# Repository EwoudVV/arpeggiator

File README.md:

# Arpeggiator

a standalone arpeggiator made from analog circuits and logic chips. no microcontroller or firmware

there are 12 note switches, arranged like one octave of a piano. turn on the notes in a chord and it plays them in ascending order. a 1/2/3-octave selector sets how many octaves it plays before repeating

with C, E and G selected, the two-octave setting plays C, E, G, then the same notes an octave higher, then starts again

## controls

- 12 latching note switches and note LEDs
- 1/2/3-octave range selector
- tempo knob and start/stop button
- tuning, decay, tone and volume knobs
- sawtooth/pulse waveform switch
- mono line output on a 3.5 mm jack
- regulated 12V DC, centre-positive 5.5 x 2.1 mm plug

## how it works

a clock sets the pace. a counter and logic circuit find the next selected note, skipping notes that are switched off. the note and octave are saved in a register so the pitch stays steady between steps

a precision voltage reference and resistor ladder set the note voltages. the selected voltage, plus an octave offset, controls an analog oscillator. an envelope controls each note's volume, followed by the tone control and output buffer

the controls and connectors will fit into a printed desktop case. the plan is one custom four-layer PCB, with through-hole controls and larger surface-mount parts where practical

## progress

the PCB is routed. it's 220 x 170 mm, with four layers. the controls are on the front and most of the circuit is on the back

i started with two layers, but fitting all the ground connections around the signal tracks was getting awkward. the two inner ground planes made that much easier

the printed case is drawn too, with a removable rear cover for tuning. i'm getting the parts together now

[parts list](BOM.csv) · [buy quantities and prices](PURCHASES.csv)

some of the controls don't have 3D models yet

## files

open [arpeggiator.kicad_pro](arpeggiator.kicad_pro) in KiCad. the [main schematic](arpeggiator.kicad_sch) links the circuit sheets in [schematic](schematic)

[arpeggiator.kicad_pcb](arpeggiator.kicad_pcb) is the routed board. the [case files and assembly notes](case) include the FreeCAD model, STEP assembly and printable STLs

[fabrication files](fabrication) includes the Gerbers and bottom stencil for JLCPCB. the board uses 1 oz outer copper and 0.5 oz inner copper

[design notes](DESIGN.md)

[journal](JOURNAL.md)

[Half Life project](https://halflife.hackclub.com/projects/cmvfhc9ih000001o8aysnkf0b)

*made for Hack Club Half Life, music week*

## parts

[BOM.csv](BOM.csv) lists what goes into one build. [PURCHASES.csv](PURCHASES.csv) has the pack sizes and minimum quantities from the shops. the case and knobs use my own filament

the current quotes add up to about $359. that includes estimated postage for the oscillator and acrylic rods, but not any LCSC import charges

<details>
<summary>full parts list</summary>

| qty | part | part number | supplier |
| ---: | --- | --- | --- |
| 4 | 74HC04 | 74HC04D,653 | [LCSC](https://www.lcsc.com/product-detail/C5590.html) |
| 8 | 74HC08 | 74HC08D,653 | [LCSC](https://www.lcsc.com/product-detail/C5593.html) |
| 1 | 74HC138 | 74HC138D,653 | [LCSC](https://www.lcsc.com/product-detail/C5602.html) |
| 4 | 74HC14 | 74HC14D,653 | [LCSC](https://www.lcsc.com/product-detail/C5605.html) |
| 1 | 74HC154 | CD74HC154M96 | [LCSC](https://www.lcsc.com/product-detail/C2832236.html) |
| 4 | 74HC163 | SN74HC163DR | [LCSC](https://www.lcsc.com/product-detail/C338758.html) |
| 7 | 74HC32 | 74HC32D,653 | [LCSC](https://www.lcsc.com/product-detail/C5632.html) |
| 3 | 74HC377 | 74HC377D,653 | [LCSC](https://www.lcsc.com/product-detail/C5639.html) |
| 1 | 74HC4051D | 74HC4051D,653 | [LCSC](https://www.lcsc.com/product-detail/C9386.html) |
| 4 | 74HC574 | 74HC574D,653 | [LCSC](https://www.lcsc.com/product-detail/C16501.html) |
| 3 | 74HC74 | 74HC74D,653 | [LCSC](https://www.lcsc.com/product-detail/C27597.html) |
| 2 | 74HC86 | 74HC86D,653 | [LCSC](https://www.lcsc.com/product-detail/C5955.html) |
| 1 | ADG706BRUZ | ADG706BRUZ-REEL7 | [LCSC](https://www.lcsc.com/product-detail/C408400.html) |
| 1 | AS3340A | AS3340A | [Infinite Machinery](https://infinitemachinery.com/as3340a) |
| 1 | CD74HC4067M | CD74HC4067M | [LCSC](https://www.lcsc.com/product-detail/C1545936.html) |
| 1 | L7805CV | L7805CV | [LCSC](https://www.lcsc.com/product-detail/C111887.html) |
| 1 | L7905CV | L7905CV | [LCSC](https://www.lcsc.com/product-detail/C111884.html) |
| 1 | LM13700M/NOPB | LM13700M/NOPB | [LCSC](https://www.lcsc.com/product-detail/C1346265.html) |
| 1 | LT1054CP | LT1054CP | [Mouser](https://www.mouser.com/en/ProductDetail/Texas-Instruments/LT1054CP?qs=p6YqzpSxLIw2yA3OFyb6XA%3D%3D) |
| 1 | MCP100T-450I/TT | MCP100T-450I/TT | [LCSC](https://www.lcsc.com/product-detail/C134467.html) |
| 2 | OPA4192IDR | OPA4192IDR | [LCSC](https://www.lcsc.com/product-detail/C2057908.html) |
| 1 | TL074HIDR | TL074HIDR | [LCSC](https://www.lcsc.com/product-detail/C2878713.html) |
| 2 | TL431BIDBZR | TL431BIDBZR | [LCSC](https://www.lcsc.com/product-detail/C41283.html) |
| 3 | TLC555IDR | TLC555IDR | [LCSC](https://www.lcsc.com/product-detail/C6987.html) |
| 1 | TMUX6219DGKRQ1 | TMUX6219DGKRQ1 | [LCSC](https://www.lcsc.com/product-detail/C3657022.html) |
| 1 | 1 / 2 / 3 octaves | SR2612F-0403-18R0B-D8-N | [Tayda](https://www.taydaelectronics.com/electromechanical/switches-key-pad/rotary-switch/rotary-switch-4-pole-3-position-alpha-sr2612f.html) |
| 1 | 1000u 25V | EEU-FR1E102 | [Mouser](https://www.mouser.com/en/ProductDetail/Panasonic/EEU-FR1E102?qs=Ao3mORb5HCARq2G4MnAlEQ%3D%3D) |
| 4 | 100k 0.01% 25ppm/C | RNCF0805TKT100K | [Mouser](https://www.mouser.com/en/ProductDetail/SEI-Stackpole/RNCF0805TKT100K?qs=IPgv5n7u5QbwSiCWZtnkOw%3D%3D) |
| 1 | 100k audio volume | RD901F-40-15F-A100K | [Tayda](https://www.taydaelectronics.com/100k-ohm-logarithmic-taper-potentiometer-d-shaft-pcb-9mm.html) |
| 1 | 100k coarse trim | 3296W-1-104LF | [LCSC](https://www.lcsc.com/product-detail/C48084.html) |
| 1 | 100k offset null | 3296W-1-104LF | [LCSC](https://www.lcsc.com/product-detail/C48084.html) |
| 1 | 100k tone | RD901F-40-15F-B100K | [Tayda](https://www.taydaelectronics.com/100k-ohm-linear-taper-potentiometer-d-shaft-pcb-9mm.html) |
| 1 | 100k tune | RD901F-40-15F-B100K | [Tayda](https://www.taydaelectronics.com/100k-ohm-linear-taper-potentiometer-d-shaft-pcb-9mm.html) |
| 2 | 100n film 100V 5% | R82EC3100DQ70J | [Tayda](https://www.taydaelectronics.com/0-1uf-100v-5-kemet-polyester-film-box-type-capacitor.html) |
| 2 | 100u 25V | EEU-FC1E101S | [Mouser](https://www.mouser.com/en/ProductDetail/Panasonic/EEU-FC1E101S?qs=XZT10BZ%2FaGG7SbPLggsp3w%3D%3D) |
| 4 | 10k 0.01% 25ppm/C | RNCF0805TKY10K0 | [Mouser](https://www.mouser.com/en/ProductDetail/SEI-Stackpole/RNCF0805TKY10K0?qs=FESYatJ8odKPVkqigBJMsg%3D%3D) |
| 1 | 10k tempco | 3296W-1-103LF | [Mouser](https://www.mouser.com/en/ProductDetail/Bourns/3296W-1-103LF?qs=CL3xLxiry19Id6AEaxYcng%3D%3D) |
| 1 | 1M decay | RD901F-40-15F-B1M | [Tayda](https://www.taydaelectronics.com/potentiometer-variable-resistors/rotary-potentiometer/linear/1m-ohm-linear-taper-potentiometer-d-shaft-pcb-9mm.html) |
| 1 | 1u film 63V 5% | R82DC4100DQ60J | [Tayda](https://www.taydaelectronics.com/1uf-63v-5-kemet-polyester-film-box-type-capacitor.html) |
| 1 | 2.2u film 100V 10% | MKS4D042204F00KSSD | [Tayda](https://www.taydaelectronics.com/capacitors/polyester-film-box-type-capacitors/wima-2200nf-2-2uf-100v-10-polyester-film-box-type-capacitor.html) |
| 1 | 20k HF track | 3296W-1-203LF | [LCSC](https://www.lcsc.com/product-detail/C34845.html) |
| 1 | 250k linear | RD901F-40-15F-B250K | [Tayda](https://www.taydaelectronics.com/potentiometer-variable-resistors/250k-ohm-linear-taper-potentiometer-d-shaft-pcb-9mm.html) |
| 2 | 2N7002 | 2N7002,215 | [LCSC](https://www.lcsc.com/product-detail/C65189.html) |
| 1 | 3.5mm mono line out | PJ-3001F | [Tayda](https://www.taydaelectronics.com/pj-3001f-3-5-mm-mono-phone-jack.html) |
| 1 | 470n film 63V 5% | R82DC3470AA60J | [Mouser](https://www.mouser.com/en/ProductDetail/KEMET/R82DC3470AA60J?qs=06HLYMEcjuWhk0f5YvbbSQ%3D%3D) |
| 3 | 47u 25V | 25YXJ47M5X11 | [Mouser](https://www.mouser.com/en/ProductDetail/Rubycon/25YXJ47M5X11?qs=T3oQrply3y%2F3J8S0Pc4Y1g%3D%3D) |
| 1 | 500 scale | 3296W-1-501LF | [Mouser](https://www.mouser.com/en/ProductDetail/Bourns/3296W-1-501LF?qs=jv1NtkgVBglZfwkzTzmOUg%3D%3D) |
| 1 | A | 1MS1T1B1M2QES | [Tayda](https://www.taydaelectronics.com/electromechanical/switches-key-pad/toggle-switch/mini-toggle-switch-spdt-on-none-on-pc-thru-hole.html) |
| 1 | A sharp | 1MS1T1B1M2QES | [Tayda](https://www.taydaelectronics.com/electromechanical/switches-key-pad/toggle-switch/mini-toggle-switch-spdt-on-none-on-pc-thru-hole.html) |
| 1 | AO3401A | AO3401A | [LCSC](https://www.lcsc.com/product-detail/C15127.html) |
| 1 | B | 1MS1T1B1M2QES | [Tayda](https://www.taydaelectronics.com/electromechanical/switches-key-pad/toggle-switch/mini-toggle-switch-spdt-on-none-on-pc-thru-hole.html) |
| 2 | BAT54GW | BAT54GWX | [LCSC](https://www.lcsc.com/product-detail/C5952163.html) |
| 1 | BAT54S,215 | BAT54S,215 | [LCSC](https://www.lcsc.com/product-detail/C47546.html) |
| 1 | BSS84 | BSS84,215 | [LCSC](https://www.lcsc.com/product-detail/C493579.html) |
| 1 | BZT52C8V2 | BZT52-C8V2J | [Mouser](https://www.mouser.com/en/ProductDetail/Nexperia/BZT52-C8V2J?qs=%252BEew9%252B0nqrCU1UOFPtFF2A%3D%3D) |
| 1 | C | 1MS1T1B1M2QES | [Tayda](https://www.taydaelectronics.com/electromechanical/switches-key-pad/toggle-switch/mini-toggle-switch-spdt-on-none-on-pc-thru-hole.html) |
| 1 | C sharp | 1MS1T1B1M2QES | [Tayda](https://www.taydaelectronics.com/electromechanical/switches-key-pad/toggle-switch/mini-toggle-switch-spdt-on-none-on-pc-thru-hole.html) |
| 1 | D | 1MS1T1B1M2QES | [Tayda](https://www.taydaelectronics.com/electromechanical/switches-key-pad/toggle-switch/mini-toggle-switch-spdt-on-none-on-pc-thru-hole.html) |
| 1 | D sharp | 1MS1T1B1M2QES | [Tayda](https://www.taydaelectronics.com/electromechanical/switches-key-pad/toggle-switch/mini-toggle-switch-spdt-on-none-on-pc-thru-hole.html) |
| 1 | E | 1MS1T1B1M2QES | [Tayda](https://www.taydaelectronics.com/electromechanical/switches-key-pad/toggle-switch/mini-toggle-switch-spdt-on-none-on-pc-thru-hole.html) |
| 1 | F | 1MS1T1B1M2QES | [Tayda](https://www.taydaelectronics.com/electromechanical/switches-key-pad/toggle-switch/mini-toggle-switch-spdt-on-none-on-pc-thru-hole.html) |
| 1 | F sharp | 1MS1T1B1M2QES | [Tayda](https://www.taydaelectronics.com/electromechanical/switches-key-pad/toggle-switch/mini-toggle-switch-spdt-on-none-on-pc-thru-hole.html) |
| 1 | G | 1MS1T1B1M2QES | [Tayda](https://www.taydaelectronics.com/electromechanical/switches-key-pad/toggle-switch/mini-toggle-switch-spdt-on-none-on-pc-thru-hole.html) |
| 1 | G sharp | 1MS1T1B1M2QES | [Tayda](https://www.taydaelectronics.com/electromechanical/switches-key-pad/toggle-switch/mini-toggle-switch-spdt-on-none-on-pc-thru-hole.html) |
| 1 | LM4040A25IDBZR | LM4040A25IDBZR | [LCSC](https://www.lcsc.com/product-detail/C9421.html) |
| 1 | MF-MSMF035/33X-2 / 350mA | MF-MSMF035/33X-2 | [Mouser](https://www.mouser.com/en/ProductDetail/Bourns/MF-MSMF035-33X-2?qs=CoAU%2FpHVZXxuOeHMuQc7RQ%3D%3D) |
| 2 | MMBT3904 | MMBT3904,215 | [LCSC](https://www.lcsc.com/product-detail/C426835.html) |
| 3 | MMBT3906 | MMBT3906,215 | [LCSC](https://www.lcsc.com/product-detail/C75549.html) |
| 1 | PESD5V0S1BA,115 | PESD5V0S1BA,115 | [LCSC](https://www.lcsc.com/product-detail/C19224.html) |
| 1 | PJ-102AH / 12V DC centre + | PJ-102AH | [Mouser](https://www.mouser.com/en/ProductDetail/Same-Sky/PJ-102AH?qs=WyjlAZoYn50Yq4CrVLCXLw%3D%3D) |
| 1 | SMBJ12A | SMBJ12A | [Mouser](https://www.mouser.com/en/ProductDetail/Littelfuse/SMBJ12A?qs=JJML70Qc14s9i3D6UUa43Q%3D%3D) |
| 3 | SS14 | SS14-E3/61T | [Mouser](https://www.mouser.com/en/ProductDetail/Vishay/SS14-E3-61T?qs=x2jpVgRnAtMLNL7KZbtr8g%3D%3D) |
| 1 | saw / pulse | 1MS1T1B1M2QES | [Tayda](https://www.taydaelectronics.com/electromechanical/switches-key-pad/toggle-switch/mini-toggle-switch-spdt-on-none-on-pc-thru-hole.html) |
| 1 | start / stop | B3F-4055 | [LCSC](https://www.lcsc.com/product-detail/C84931.html) |
| 1 | 1.1M 1% | RC0805FR-071M1L | [Mouser](https://www.mouser.com/en/ProductDetail/YAGEO/RC0805FR-071M1L?qs=g6xwsc4j%252B%2FrRMnxWx%2Fruqg%3D%3D) |
| 2 | 1.5M 1% | RC0805FR-071M5L | [Mouser](https://www.mouser.com/en/ProductDetail/YAGEO/RC0805FR-071M5L?qs=g6xwsc4j%252B%2FoVoMODI3Rz0Q%3D%3D) |
| 1 | 1.5k 1% | RC0805FR-071K5L | [Mouser](https://www.mouser.com/en/ProductDetail/YAGEO/RC0805FR-071K5L?qs=8Y8p%252BasKcI6LbaohOVk4HA%3D%3D) |
| 1 | 1.82M 0.1% | CPF0805B1M82E | [Mouser](https://www.mouser.com/en/ProductDetail/TE-Connectivity/CPF0805B1M82E?qs=CXI0wBT1M2hvtJld3NhfsA%3D%3D) |
| 1 | 1.8M 1% | ERJ-6ENF1804V | [Mouser](https://www.mouser.com/en/ProductDetail/Panasonic/ERJ-6ENF1804V?qs=JjxTDIFmKPTXgJmgM%2FyOiQ%3D%3D) |
| 1 | 100 0.1% | RT0805BRD07100RL | [Mouser](https://www.mouser.com/en/ProductDetail/YAGEO/RT0805BRD07100RL?qs=%2Ff7pOCXLR5dUTF5MWPONjg%3D%3D) |
| 11 | 100k 1% | RC0805FR-07100KL | [Mouser](https://www.mouser.com/en/ProductDetail/YAGEO/RC0805FR-07100KL?qs=8Y8p%252BasKcI7rEWn6FcVdAA%3D%3D) |
| 1 | 100n 5% | C0805C104J5RACTU | [Mouser](https://www.mouser.com/en/ProductDetail/KEMET/C0805C104J5RACTU?qs=gbgtKHXraGH15GhoNPXHBg%3D%3D) |
| 68 | 100n 50V X7R 10% | CC0805KRX7R9BB104 | [LCSC](https://www.lcsc.com/product-detail/C49678.html) |
| 5 | 100p C0G | C0805C101J5GACTU | [Mouser](https://www.mouser.com/en/ProductDetail/KEMET/C0805C101J5GACTU?qs=6pfgPk%252B7Yz7wCPQSSQ%2FBjg%3D%3D) |
| 2 | 10k 0.1% | RT0805BRD0710KL | [Mouser](https://www.mouser.com/en/ProductDetail/YAGEO/RT0805BRD0710KL?qs=87%2Fgv35YuOdOfU%252BBkLDVxA%3D%3D) |
| 1 | 10k 0.1% 25ppm/C | RT0805BRD0710KL | [Mouser](https://www.mouser.com/en/ProductDetail/YAGEO/RT0805BRD0710KL?qs=87%2Fgv35YuOdOfU%252BBkLDVxA%3D%3D) |
| 25 | 10k 1% | RC0805FR-0710KL | [Mouser](https://www.mouser.com/en/ProductDetail/YAGEO/RC0805FR-0710KL?qs=7bY8808IzHq6vrU3BeiiYw%3D%3D) |
| 6 | 10n | C0805C103J5GACTU | [LCSC](https://www.lcsc.com/product-detail/C2167597.html) |
| 1 | 10u 16V | GRM21BR61C106KE15L | [LCSC](https://www.lcsc.com/product-detail/C77075.html) |
| 1 | 15k 0.1% 25ppm/C | RT0805BRD0715KL | [Mouser](https://www.mouser.com/en/ProductDetail/YAGEO/RT0805BRD0715KL?qs=%2Ff7pOCXLR5foXQ1VlhQYhQ%3D%3D) |
| 1 | 174k 0.1% | RT0805BRD07174KL | [Mouser](https://www.mouser.com/en/ProductDetail/YAGEO/RT0805BRD07174KL?qs=4CyHz7GXqSj4xC7rYoRg0A%3D%3D) |
| 1 | 18.2k 1% | ERJ-6ENF1822V | [Mouser](https://www.mouser.com/en/ProductDetail/Panasonic/ERJ-6ENF1822V?qs=JjxTDIFmKPRzh6ImPVU9cQ%3D%3D) |
| 2 | 1M 1% | RC0805FR-071ML | [Mouser](https://www.mouser.com/en/ProductDetail/YAGEO/RC0805FR-071ML?qs=8Y8p%252BasKcI6wvSL4jxV1pQ%3D%3D) |
| 12 | 1k 0.1% | RT0805BRD071KL | [Mouser](https://www.mouser.com/en/ProductDetail/YAGEO/RT0805BRD071KL?qs=%2Ff7pOCXLR5e3FpClshTdPA%3D%3D) |
| 6 | 1k 1% | RC0805FR-071KL | [Mouser](https://www.mouser.com/en/ProductDetail/YAGEO/RC0805FR-071KL?qs=1ogmaHw32WJjeGY0DHXakQ%3D%3D) |
| 2 | 1n C0G | C0805C102J5GACTU | [Mouser](https://www.mouser.com/en/ProductDetail/KEMET/C0805C102J5GACTU?qs=yrVqjCObULOWvTzsHVJg1Q%3D%3D) |
| 12 | 1u 16V | CC0805KKX7R8BB105 | [Mouser](https://www.mouser.com/en/ProductDetail/YAGEO/CC0805KKX7R8BB105?qs=QENzi4TkIJ0C75LKGblEtw%3D%3D) |
| 14 | 2.2k 1% | RC0805FR-072K2L | [Mouser](https://www.mouser.com/en/ProductDetail/YAGEO/RC0805FR-072K2L?qs=CSLd874fYV2eT6iKTza3nw%3D%3D) |
| 1 | 2.32k 0.1% | RT0805BRD072K32L | [Mouser](https://www.mouser.com/en/ProductDetail/YAGEO/RT0805BRD072K32L?qs=4CyHz7GXqSgSJcxnTJ8TbQ%3D%3D) |
| 1 | 2.49k 1% | RC0805FR-072K49L | [Mouser](https://www.mouser.com/en/ProductDetail/YAGEO/RC0805FR-072K49L?qs=QrWOOBGzeCbaR%2FeulLJohg%3D%3D) |
| 1 | 200k 1% | RC0805FR-07200KL | [Mouser](https://www.mouser.com/en/ProductDetail/YAGEO/RC0805FR-07200KL?qs=8Y8p%252BasKcI4ufYuYh%252BmyZQ%3D%3D) |
| 1 | 20k 0.1% | RT0805BRD0720KL | [Mouser](https://www.mouser.com/en/ProductDetail/YAGEO/RT0805BRD0720KL?qs=87%2Fgv35YuOd%2FdRM1LyX3Lg%3D%3D) |
| 2 | 220 1% | RC0805FR-07220RL | [Mouser](https://www.mouser.com/en/ProductDetail/YAGEO/RC0805FR-07220RL?qs=KCkj9j0IqmXa4o%252BHKR6RGw%3D%3D) |
| 1 | 22k 1% | RC0805FR-0722KL | [Mouser](https://www.mouser.com/en/ProductDetail/YAGEO/RC0805FR-0722KL?qs=ngJqVwYVsdVbc7Rh0xIeHw%3D%3D) |
| 1 | 24k 1% | RC0805FR-0724KL | [Mouser](https://www.mouser.com/en/ProductDetail/YAGEO/RC0805FR-0724KL?qs=0OpHuDRjTADBsy5P0J6k2w%3D%3D) |
| 2 | 2k 0.1% | RT0805BRD072KL | [Mouser](https://www.mouser.com/en/ProductDetail/YAGEO/RT0805BRD072KL?qs=7JGxMcfkPok2189RXPA53g%3D%3D) |
| 1 | 2n C0G | C0805C202J5GACTU | [Mouser](https://www.mouser.com/en/ProductDetail/KEMET/C0805C202J5GACTU?qs=W4SVoLh3QChWIjbVvPwmQg%3D%3D) |
| 2 | 330k 0.1% | RT0805BRD07330KL | [Mouser](https://www.mouser.com/en/ProductDetail/YAGEO/RT0805BRD07330KL?qs=aZCcseWLxnuj6nToWrZKFA%3D%3D) |
| 1 | 330n 50V | C0805C334K5RACTU | [Mouser](https://www.mouser.com/en/ProductDetail/KEMET/C0805C334K5RACTU?qs=nRD1PKnFC2Hh3tSy%2FGeH2Q%3D%3D) |
| 1 | 33k 1% | RC0805FR-0733KL | [Mouser](https://www.mouser.com/en/ProductDetail/YAGEO/RC0805FR-0733KL?qs=BrN8wpjQTgGzZxKgikrwvw%3D%3D) |
| 1 | 33p C0G | C0805C330J5GACTU | [Mouser](https://www.mouser.com/en/ProductDetail/KEMET/C0805C330J5GACTU?qs=PVnqbTyV3SUE6Uu%252BkD9Iyg%3D%3D) |
| 1 | 360k 0.1% | RT0805BRD07360KL | [Mouser](https://www.mouser.com/en/ProductDetail/YAGEO/RT0805BRD07360KL?qs=aZCcseWLxnvpELpsSQnh8g%3D%3D) |
| 1 | 36k 1% | RC0805FR-0736KL | [Mouser](https://www.mouser.com/en/ProductDetail/YAGEO/RC0805FR-0736KL?qs=g6xwsc4j%252B%2Fq3CmSeyDlL7g%3D%3D) |
| 1 | 4.7 1% 0.25W | RC1206FR-074R7L | [Mouser](https://www.mouser.com/en/ProductDetail/YAGEO/RC1206FR-074R7L?qs=bz%2FLPVPAsTK5WyYax3BLuA%3D%3D) |
| 1 | 4.7u 25V X7R | GRM21BR71E475KA73L | [LCSC](https://www.lcsc.com/product-detail/C162427.html) |
| 2 | 470 1% | RC0805FR-07470RL | [Mouser](https://www.mouser.com/en/ProductDetail/YAGEO/RC0805FR-07470RL?qs=CSLd874fYV2wsnqMGLpcHA%3D%3D) |
| 5 | 47k 1% | RC0805FR-0747KL | [Mouser](https://www.mouser.com/en/ProductDetail/YAGEO/RC0805FR-0747KL?qs=sfaR5EV1ye7DERH7OnC2Gg%3D%3D) |
| 1 | 5.62k 0.1% | RT0805BRD075K62L | [Mouser](https://www.mouser.com/en/ProductDetail/YAGEO/RT0805BRD075K62L?qs=ylEn6CkgxuiWDc5aTJ638g%3D%3D) |
| 1 | 51k 1% | RC0805FR-0751KL | [Mouser](https://www.mouser.com/en/ProductDetail/YAGEO/RC0805FR-0751KL?qs=g6xwsc4j%252B%2FrUFmy6S6ALYQ%3D%3D) |
| 1 | 6.04k 0.1% | RT0805BRD076K04L | [Mouser](https://www.mouser.com/en/ProductDetail/YAGEO/RT0805BRD076K04L?qs=8SI67b7NHM5NwjLBwcP%252BXQ%3D%3D) |
| 1 | 6.49k 0.1% | RT0805BRD076K49L | [Mouser](https://www.mouser.com/en/ProductDetail/YAGEO/RT0805BRD076K49L?qs=4CyHz7GXqSiLdN4y1MhhhQ%3D%3D) |
| 1 | 820k 1% | RC0805FR-07820KL | [Mouser](https://www.mouser.com/en/ProductDetail/YAGEO/RC0805FR-07820KL?qs=g6xwsc4j%252B%2FozLzDoZP6Szg%3D%3D) |
| 2 | 910 1% | RC0805FR-07910RL | [Mouser](https://www.mouser.com/en/ProductDetail/YAGEO/RC0805FR-07910RL?qs=g6xwsc4j%252B%2FoZ2NamZOKACA%3D%3D) |
| 6 | copper test pad | - | with PCB |
| 1 | logic test header | M20-9990846 | [Mouser](https://www.mouser.com/en/ProductDetail/Harwin/M20-9990846?qs=ulE8k0yEMYb37YKanNqd%2FQ%3D%3D) |
| 12 | note LED, 0805 | APT2012SYCK | [Mouser](https://www.mouser.com/en/ProductDetail/Kingbright/APT2012SYCK?qs=y3UkhjaxUTb%252BLZXQu8d2yw%3D%3D) |
| 1 | four-layer PCB, 220 x 170 mm, 1.6 mm FR4, 1 oz outer / 0.5 oz inner | arpeggiator-jlcpcb | [JLCPCB](https://jlcpcb.com/pcb-fabrication/fr4-pcb) |
| 1 | printed tray, control panel, rear cover and octave collar | - | printed |
| 5 | printed pot knob | - | printed |
| 1 | regulated 12V DC adapter, >=0.5A, centre +, 5.5/2.1mm | SMI6B-12-4-P5 | [Mouser](https://www.mouser.com/en/ProductDetail/CUI-Inc/SMI6B-12-4-P5?qs=mAH9sUMRCtt8%252BS4f4Sapgw%3D%3D) |
| 1 | printed octave knob | - | printed |
| 18 | M3 x 8 mm socket-head screw | A-6393 | [Tayda](https://www.taydaelectronics.com/hardware-tools/nuts-washers-screws-spacers-and-more/screws/m3-hexagon-socket-head-cap-screw-3x8mm-grade-12-9.html) |
| 18 | M3 hex nut | Nut M3 | [Tayda](https://www.taydaelectronics.com/nut-3mm-for-screw-m3.html) |
| 4 | stick-on rubber foot, about 12 mm diameter | RF-1204 | [Tayda](https://www.taydaelectronics.com/rubber-feet-black-64pcs-block-size-12mmx4mm-for-enclosure.html) |
| 1 | clear 3 mm acrylic rod, at least 200 mm stock | a24061900ux1460 | [Harfington](https://www.harfington.com/products/p-1536182) |
| 1 | round black button cap | B32-1610 | [Mouser](https://www.mouser.com/en/ProductDetail/Aratas/B32-1610?qs=1tDaWCEHQQ6l3s6oDrKSiA%3D%3D) |
| 5 | M7 x 0.75 thin pot nut and washer | - | control hardware |
| 13 | 1/4-40 toggle nut and washer | - | control hardware |
| 1 | 3/8-32 NEF rotary nut and lockwasher | - | control hardware |
| 1 | M6 x 0.5 jack nut and washer | - | control hardware |
| 1 | bottom-side frameless stencil, 380 x 280 mm, 0.12 mm | arpeggiator-bottom-stencil | [JLCPCB](https://jlcpcb.com/pcb-stencil) |

</details>

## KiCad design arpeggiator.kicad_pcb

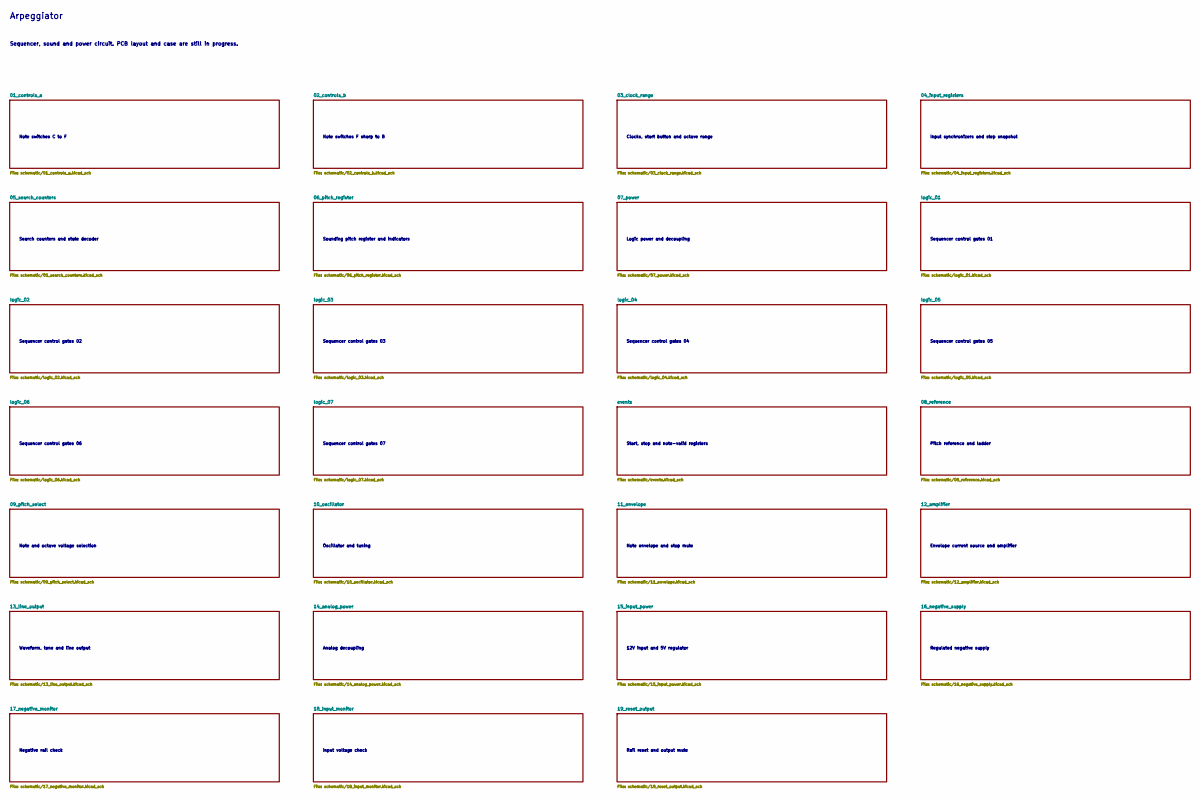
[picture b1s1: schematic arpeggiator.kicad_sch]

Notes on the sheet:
Arpeggiator
Sequencer, sound and power circuit. PCB layout and case are still in progress.
Note switches C to F
Note switches F sharp to B
Clocks, start button and octave range
Input synchronizers and step snapshot
Search counters and state decoder
Sounding pitch register and indicators
Logic power and decoupling
Sequencer control gates 01
Sequencer control gates 02
Sequencer control gates 03
Sequencer control gates 04
Sequencer control gates 05
Sequencer control gates 06
Sequencer control gates 07
Start, stop and note-valid registers
Pitch reference and ladder
Note and octave voltage selection
Oscillator and tuning
Note envelope and stop mute
Envelope current source and amplifier
Waveform, tone and line output
Analog decoupling
12V input and 5V regulator
Regulated negative supply
Negative rail check
Input voltage check
Rail reset and output mute

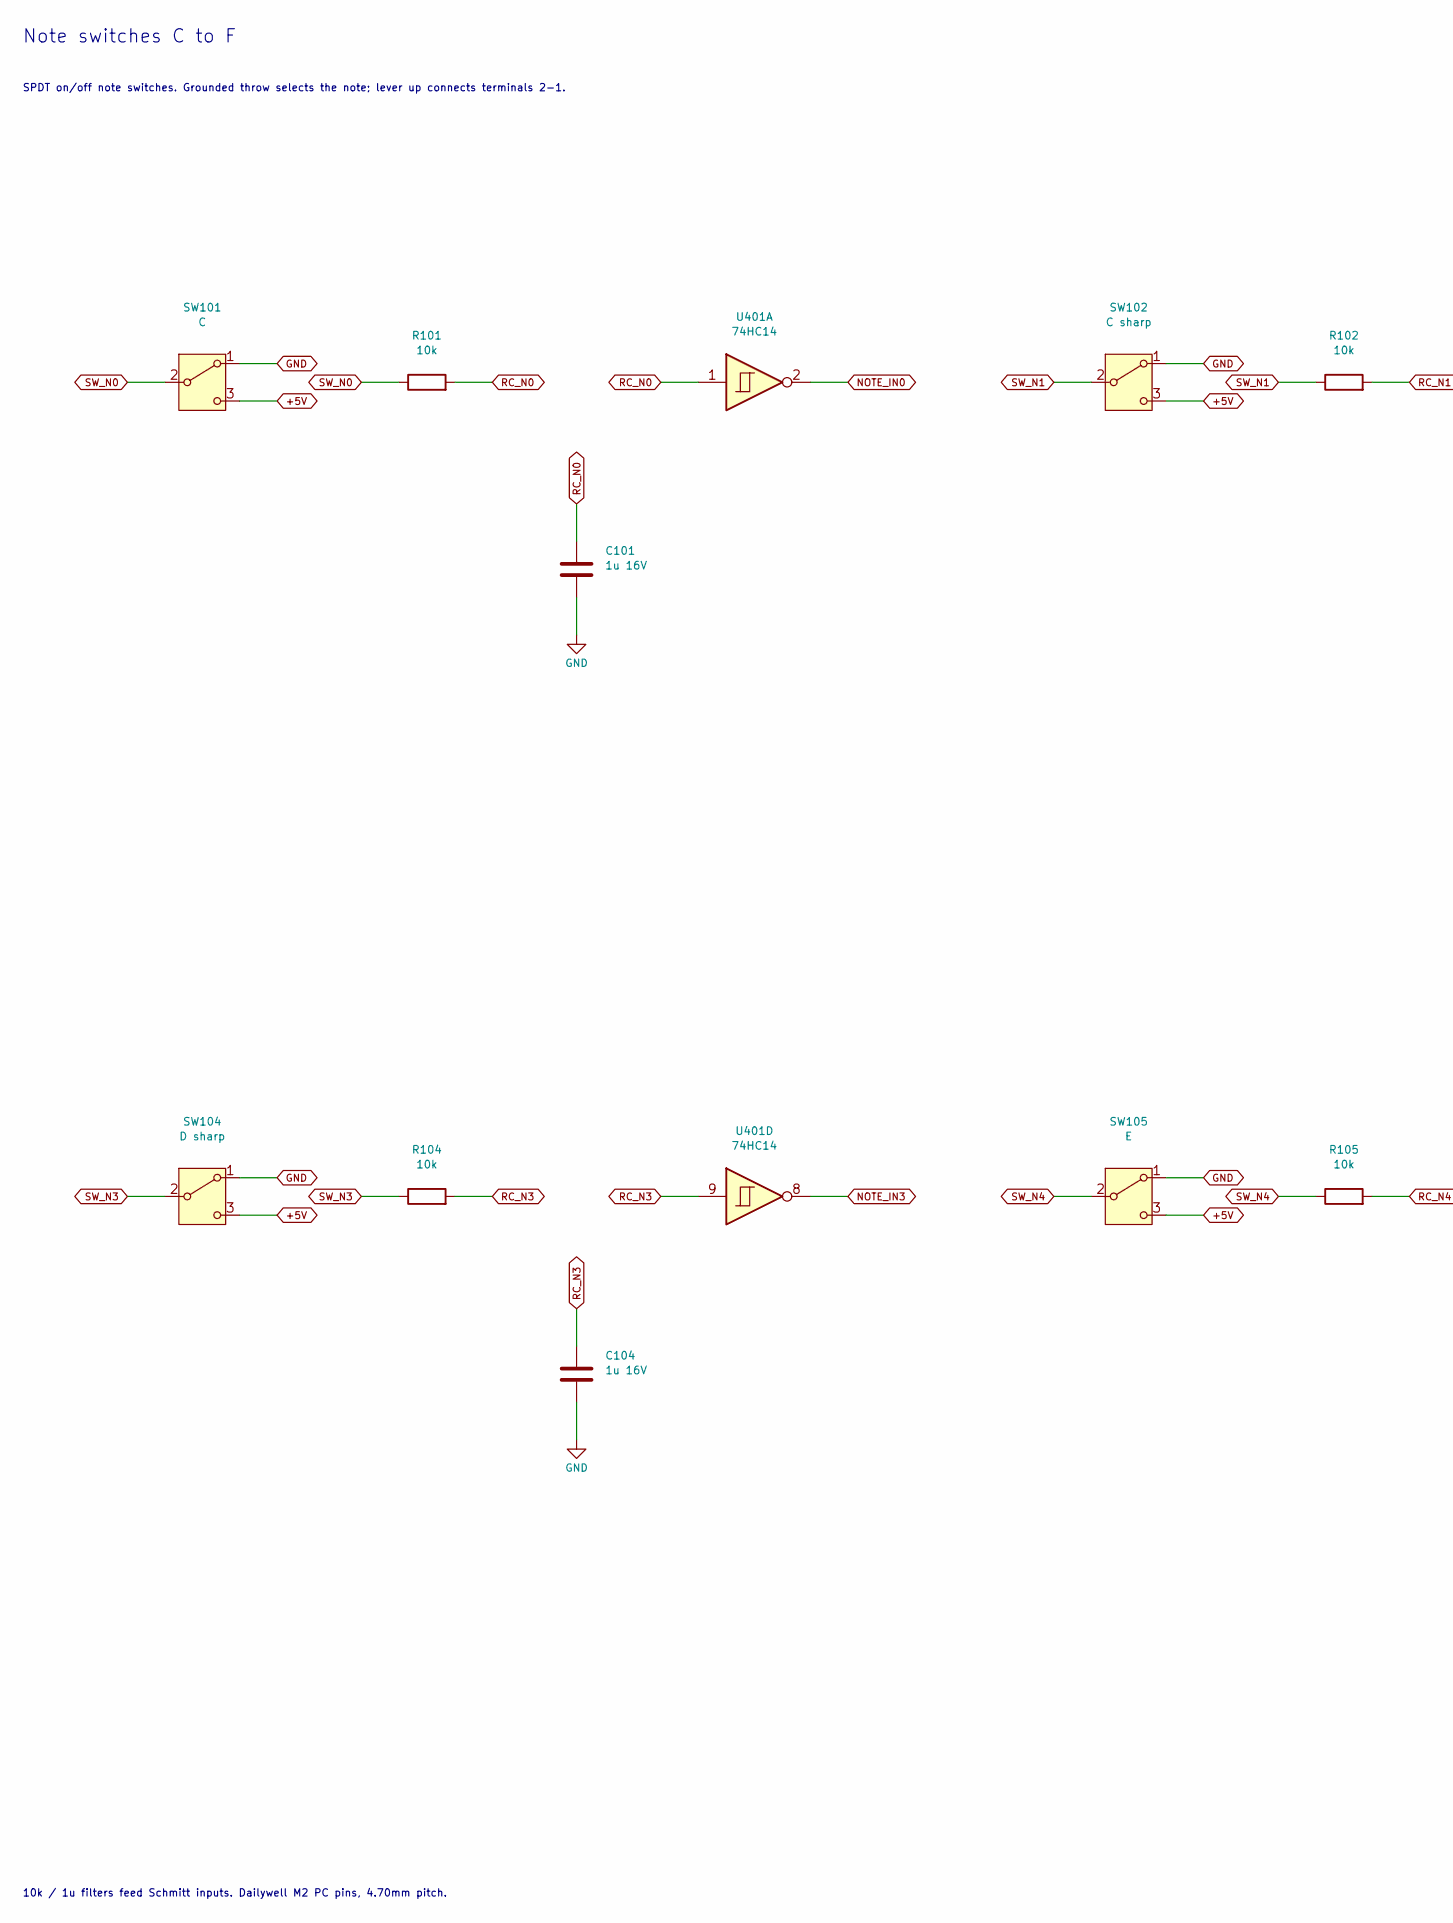
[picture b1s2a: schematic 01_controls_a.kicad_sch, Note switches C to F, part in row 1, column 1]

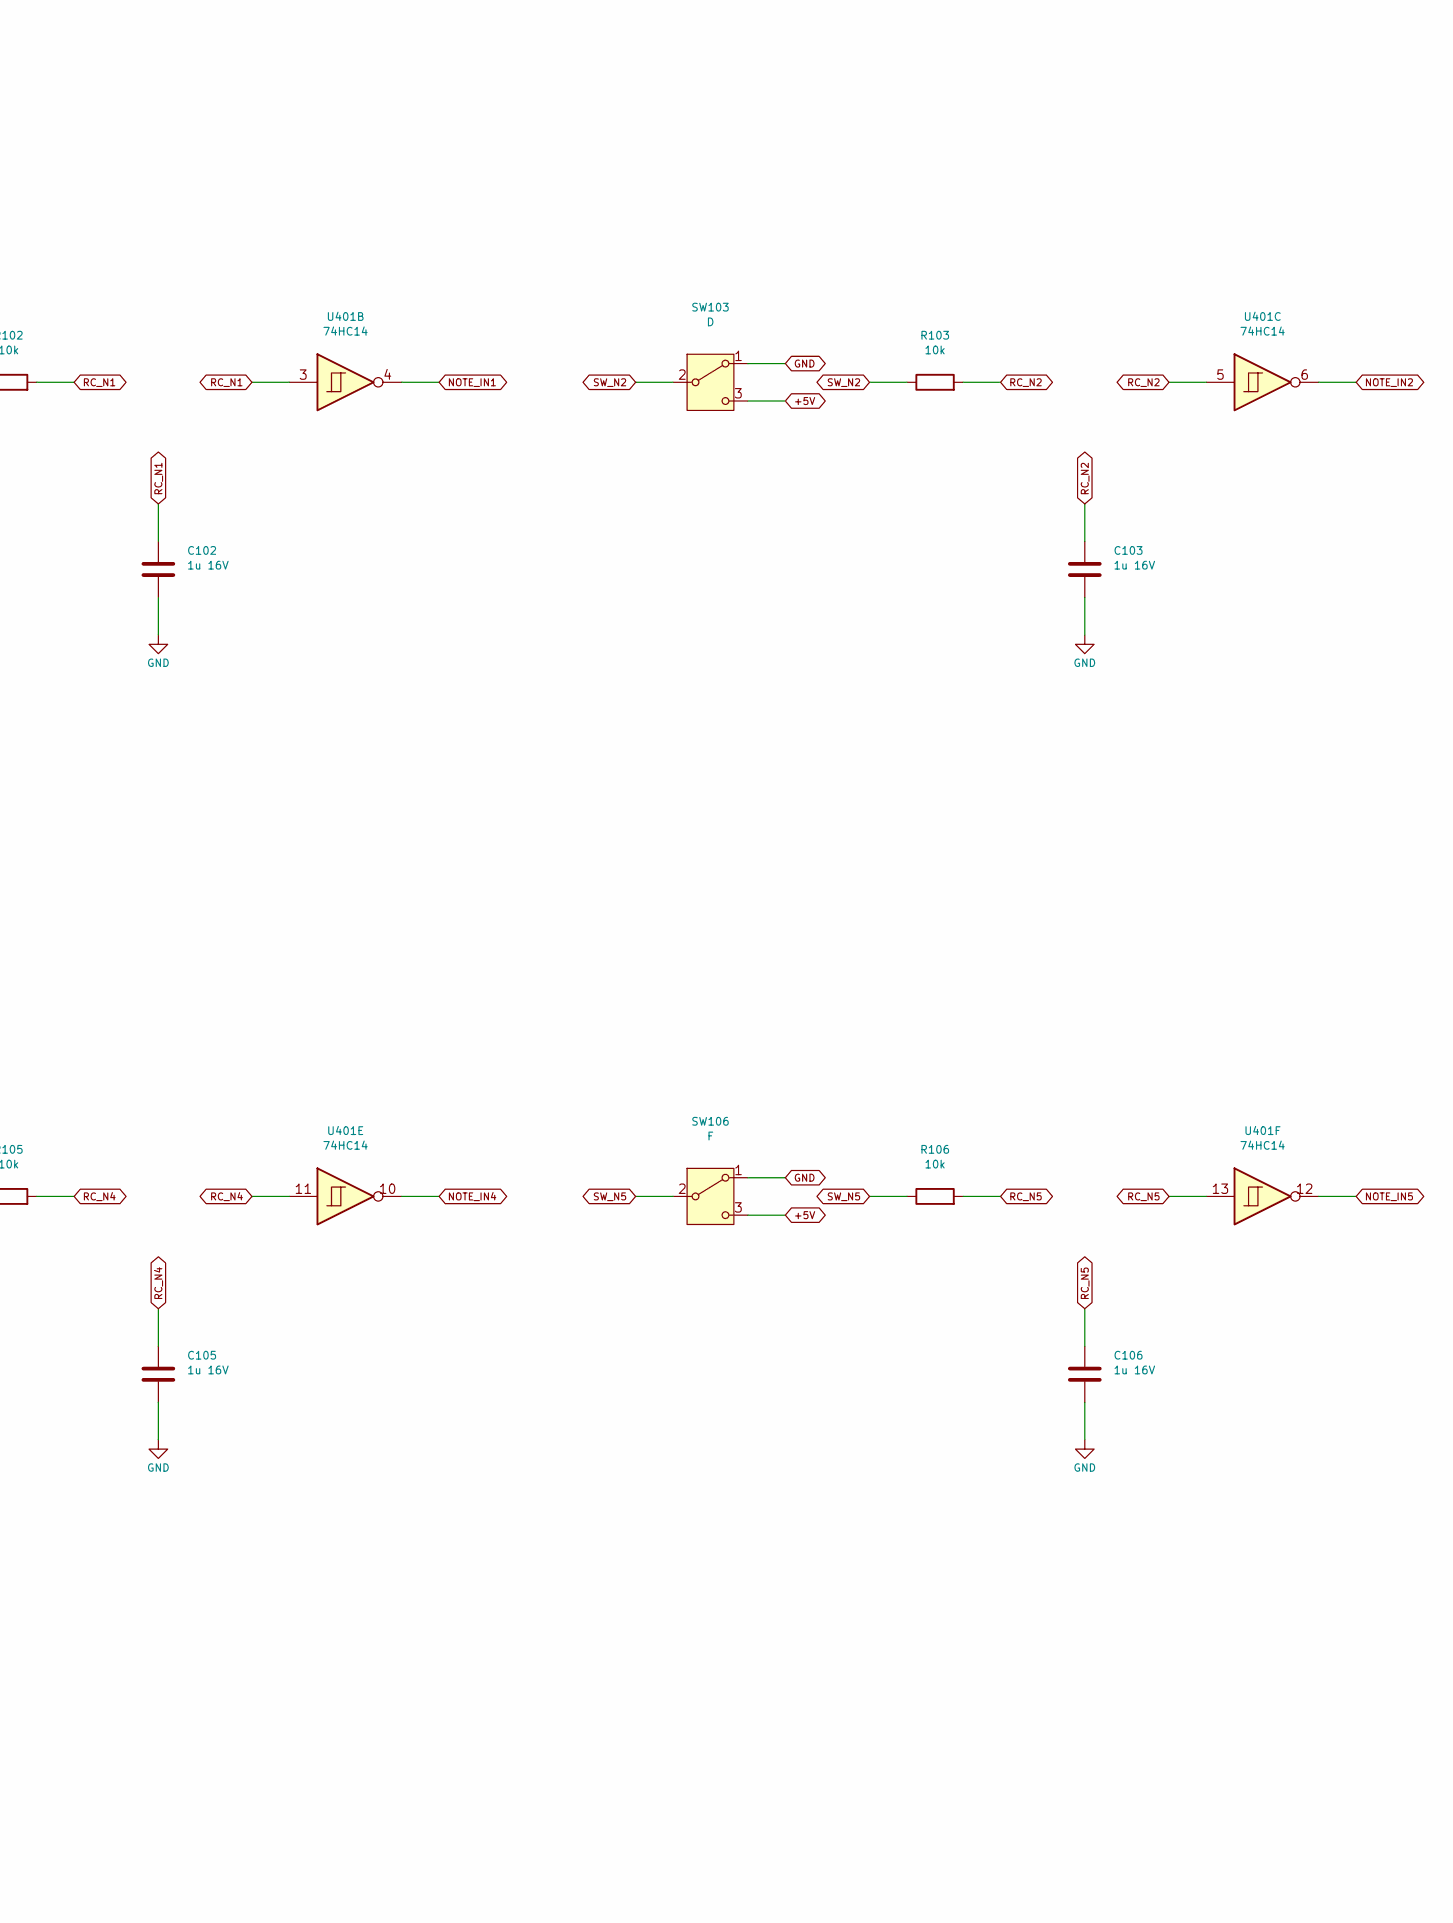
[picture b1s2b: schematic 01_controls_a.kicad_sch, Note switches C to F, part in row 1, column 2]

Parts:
C101, C102, C103, C104, C105, C106: 1u 16V; C_0805_2012Metric
R101, R102, R103, R104, R105, R106: 10k; R_0805_2012Metric
SW101: C; SW_Dailywell_1M_SPDT_M2; MPN 1MS1T1B1M2QES
SW102: C sharp; SW_Dailywell_1M_SPDT_M2; MPN 1MS1T1B1M2QES
SW103: D; SW_Dailywell_1M_SPDT_M2; MPN 1MS1T1B1M2QES
SW104: D sharp; SW_Dailywell_1M_SPDT_M2; MPN 1MS1T1B1M2QES
SW105: E; SW_Dailywell_1M_SPDT_M2; MPN 1MS1T1B1M2QES
SW106: F; SW_Dailywell_1M_SPDT_M2; MPN 1MS1T1B1M2QES
U401: 74HC14; SOIC-14_3.9x8.7mm_P1.27mm; MPN 74HC14D,653

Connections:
+5V: SW101.3 (C), SW102.3 (C), SW103.3 (C), SW104.3 (C), SW105.3 (C), SW106.3 (C); also elsewhere on the board
NOTE_IN0: U401.2; also elsewhere on the board
NOTE_IN1: U401.4; also elsewhere on the board
NOTE_IN2: U401.6; also elsewhere on the board
NOTE_IN3: U401.8; also elsewhere on the board
NOTE_IN4: U401.10; also elsewhere on the board
NOTE_IN5: U401.12; also elsewhere on the board
RC_N0: C101.1, R101.2, U401.1
RC_N1: C102.1, R102.2, U401.3
RC_N2: C103.1, R103.2, U401.5
RC_N3: C104.1, R104.2, U401.9
RC_N4: C105.1, R105.2, U401.11
RC_N5: C106.1, R106.2, U401.13
SW_N0: R101.1, SW101.2 (B)
SW_N1: R102.1, SW102.2 (B)
SW_N2: R103.1, SW103.2 (B)
SW_N3: R104.1, SW104.2 (B)
SW_N4: R105.1, SW105.2 (B)
SW_N5: R106.1, SW106.2 (B)

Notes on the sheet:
Note switches C to F
SPDT on/off note switches. Grounded throw selects the note; lever up connects terminals 2-1.
10k / 1u filters feed Schmitt inputs. Dailywell M2 PC pins, 4.70mm pitch.

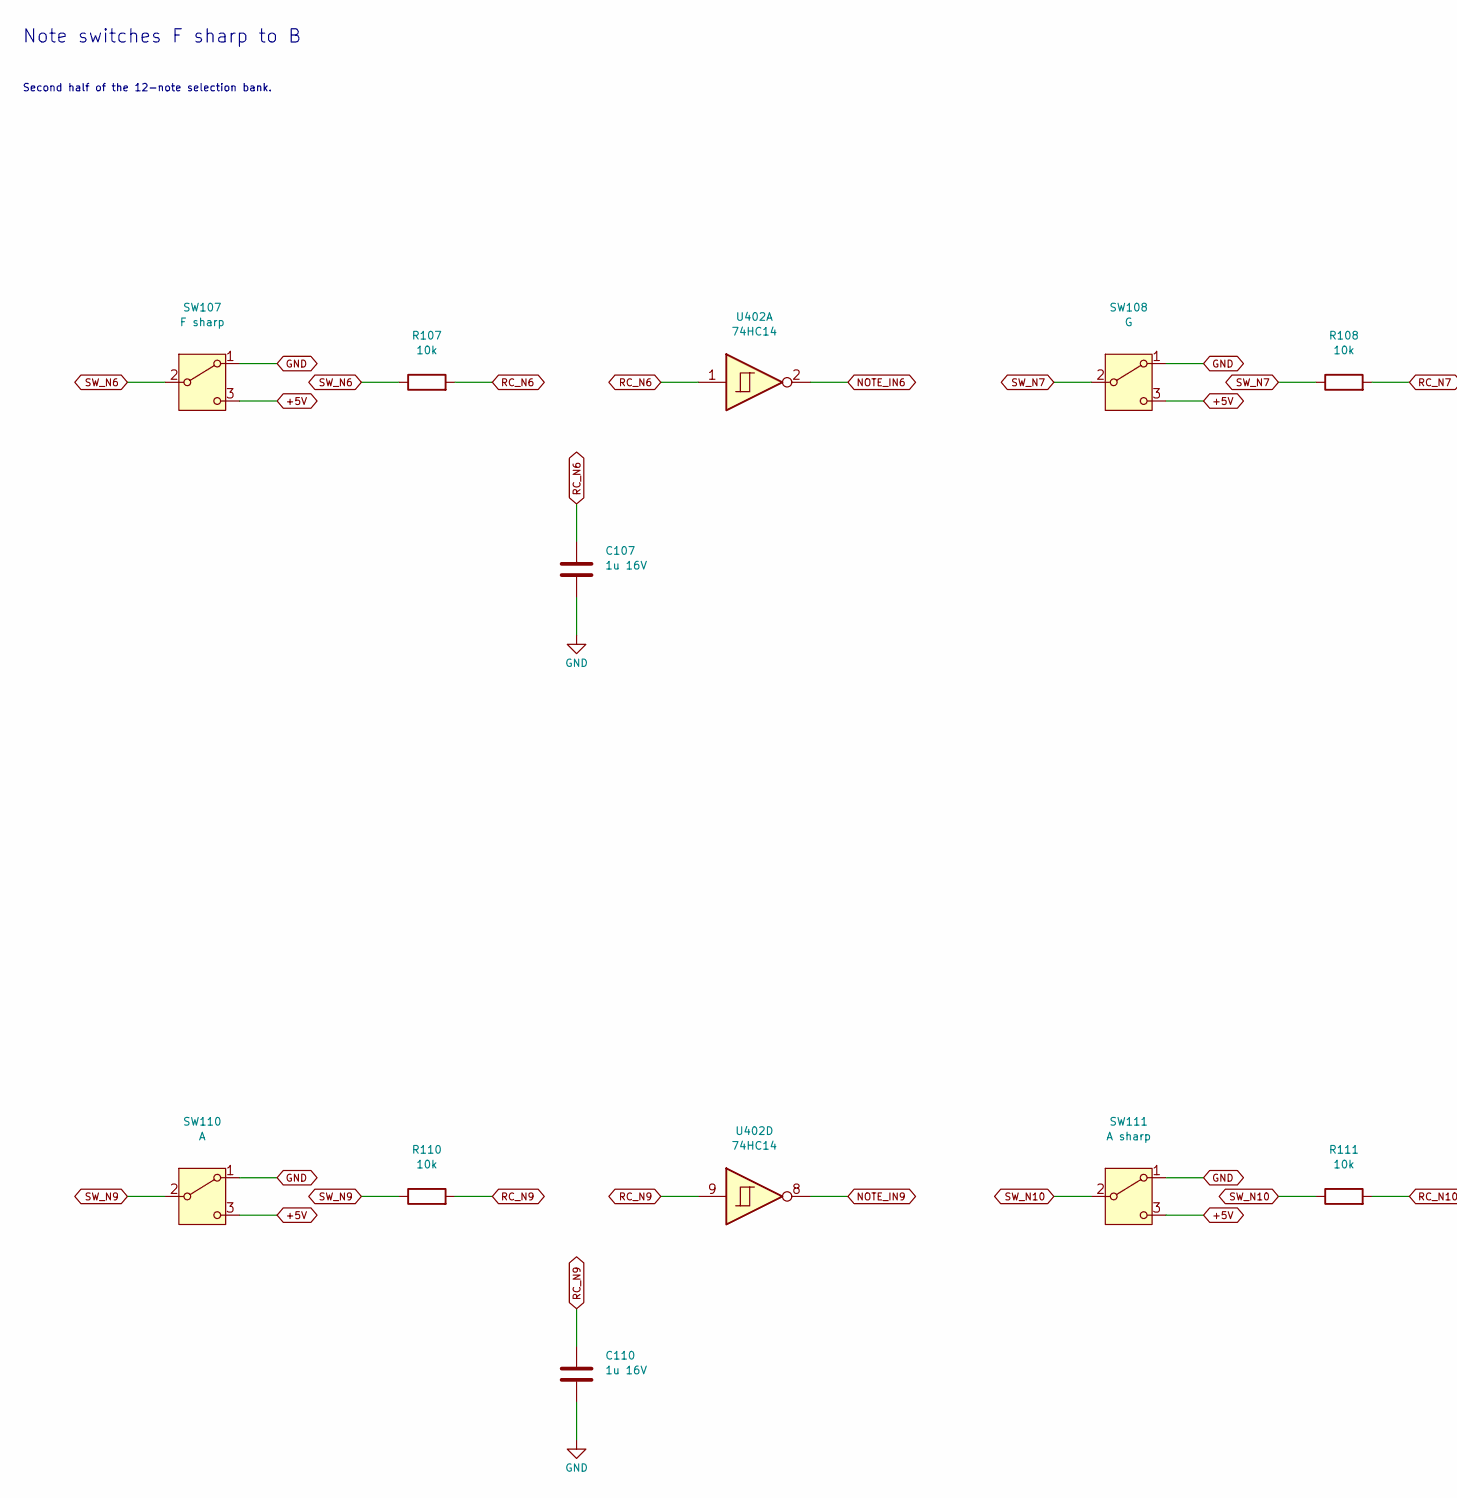
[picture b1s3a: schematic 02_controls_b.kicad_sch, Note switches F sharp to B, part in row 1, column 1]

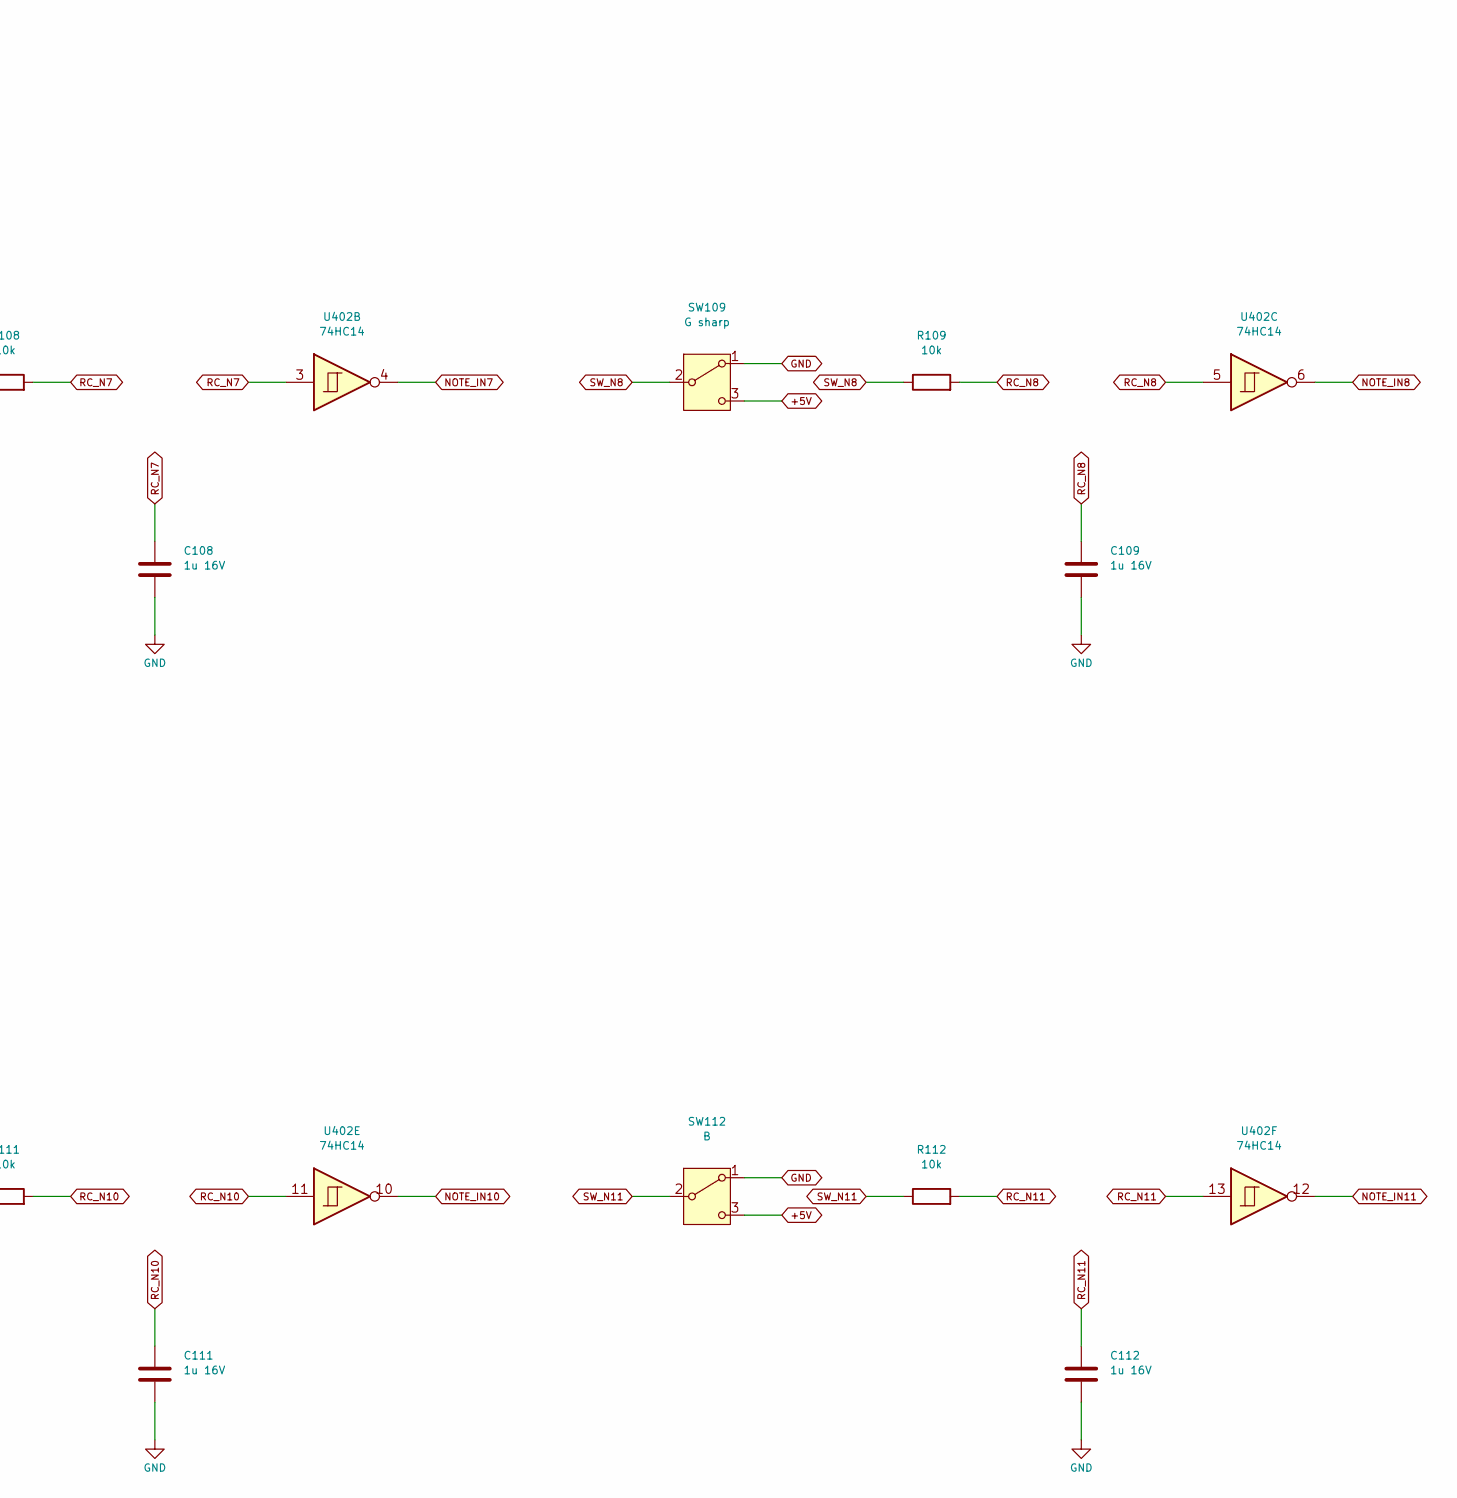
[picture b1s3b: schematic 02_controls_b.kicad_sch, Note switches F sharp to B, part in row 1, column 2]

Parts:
C107, C108, C109, C110, C111, C112: 1u 16V; C_0805_2012Metric
R107, R108, R109, R110, R111, R112: 10k; R_0805_2012Metric
SW107: F sharp; SW_Dailywell_1M_SPDT_M2; MPN 1MS1T1B1M2QES
SW108: G; SW_Dailywell_1M_SPDT_M2; MPN 1MS1T1B1M2QES
SW109: G sharp; SW_Dailywell_1M_SPDT_M2; MPN 1MS1T1B1M2QES
SW110: A; SW_Dailywell_1M_SPDT_M2; MPN 1MS1T1B1M2QES
SW111: A sharp; SW_Dailywell_1M_SPDT_M2; MPN 1MS1T1B1M2QES
SW112: B; SW_Dailywell_1M_SPDT_M2; MPN 1MS1T1B1M2QES
U402: 74HC14; SOIC-14_3.9x8.7mm_P1.27mm; MPN 74HC14D,653

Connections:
+5V: SW107.3 (C), SW108.3 (C), SW109.3 (C), SW110.3 (C), SW111.3 (C), SW112.3 (C); also elsewhere on the board
NOTE_IN6: U402.2; also elsewhere on the board
NOTE_IN7: U402.4; also elsewhere on the board
NOTE_IN8: U402.6; also elsewhere on the board
NOTE_IN9: U402.8; also elsewhere on the board
NOTE_IN10: U402.10; also elsewhere on the board
NOTE_IN11: U402.12; also elsewhere on the board
RC_N6: C107.1, R107.2, U402.1
RC_N7: C108.1, R108.2, U402.3
RC_N8: C109.1, R109.2, U402.5
RC_N9: C110.1, R110.2, U402.9
RC_N10: C111.1, R111.2, U402.11
RC_N11: C112.1, R112.2, U402.13
SW_N6: R107.1, SW107.2 (B)
SW_N7: R108.1, SW108.2 (B)
SW_N8: R109.1, SW109.2 (B)
SW_N9: R110.1, SW110.2 (B)
SW_N10: R111.1, SW111.2 (B)
SW_N11: R112.1, SW112.2 (B)

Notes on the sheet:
Note switches F sharp to B
Second half of the 12-note selection bank.
